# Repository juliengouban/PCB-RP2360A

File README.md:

# PCB-RP2360A
PCB desing file for the new raspberry RP2350A microcontroler

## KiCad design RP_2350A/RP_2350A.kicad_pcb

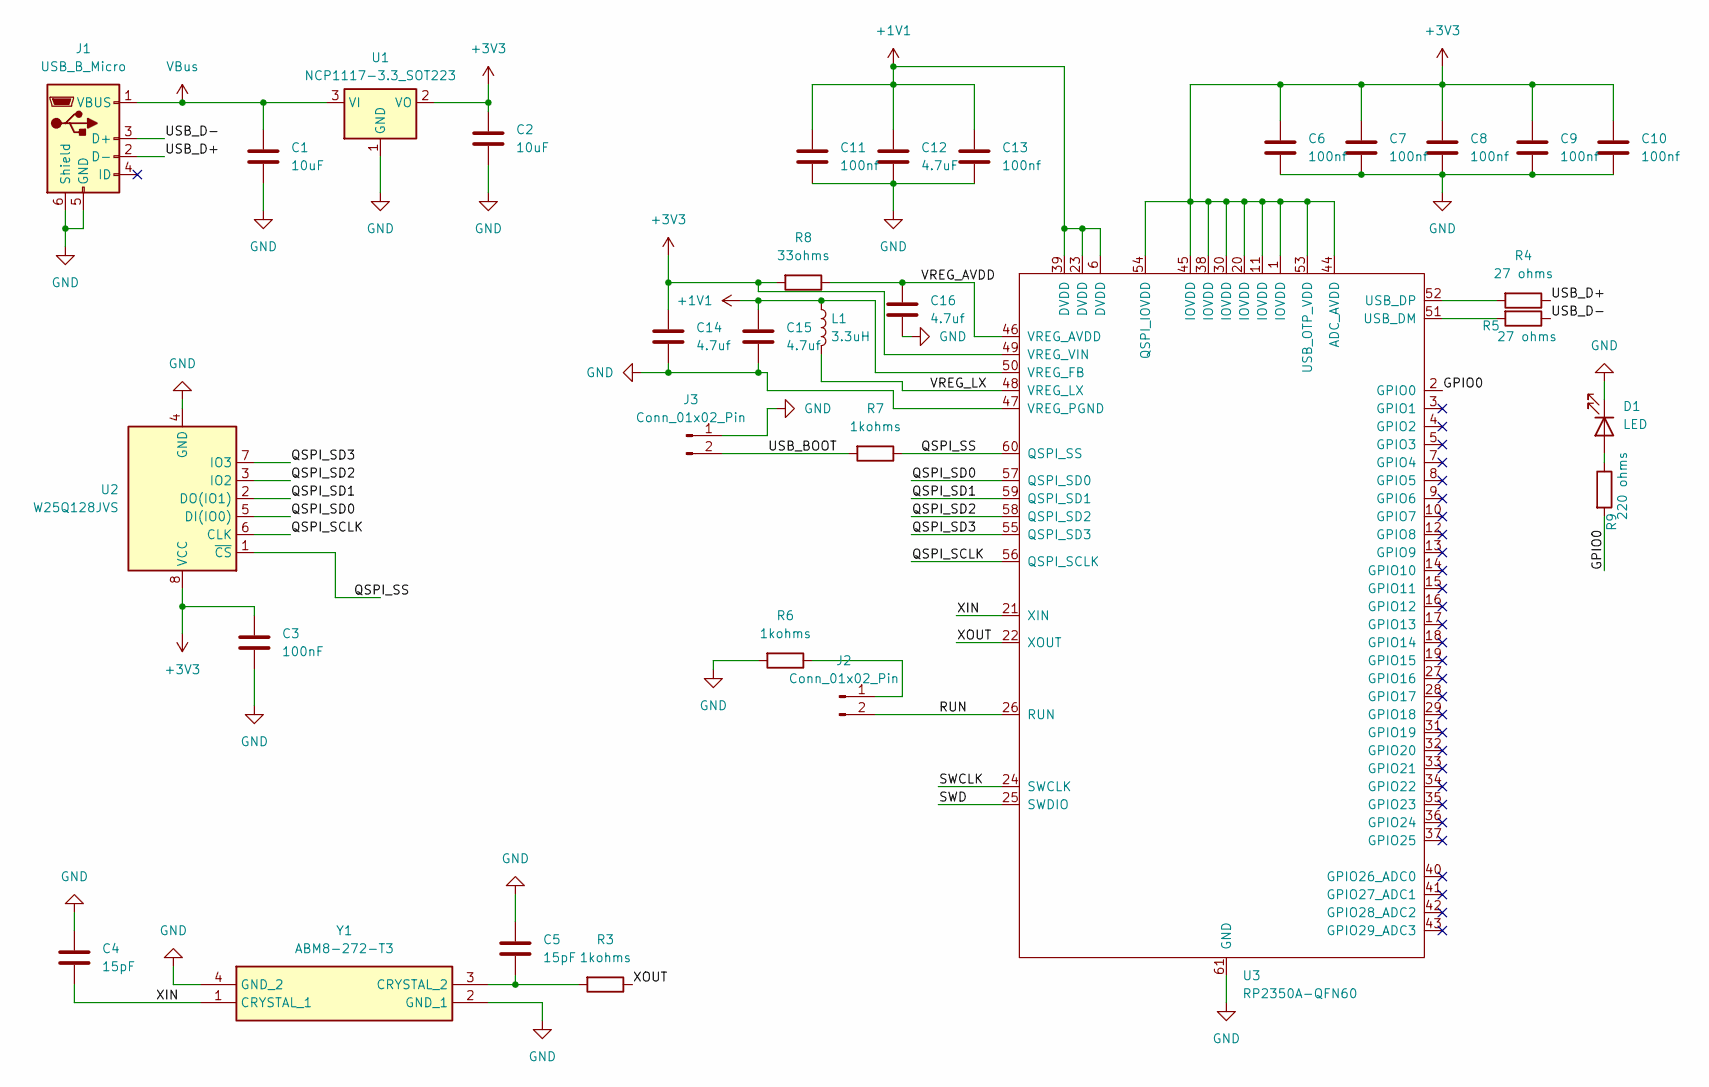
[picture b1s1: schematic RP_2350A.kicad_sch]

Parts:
C1, C2: 10uF; C_0402_1005Metric
C3: 100nF; C_0402_1005Metric
C4, C5: 15pF; C_0402_1005Metric
C6, C7, C8, C9, C10, C11, C13: 100nf; C_0402_1005Metric
C12: 4.7uF; C_0402_1005Metric
C14, C15, C16: 4.7uf; C_0402_1005Metric
D1: LED; LED_0402_1005Metric
J1: USB_B_Micro; USB_Micro-B_Amphenol_10103594-0001LF_Horizontal
J2, J3: Conn_01x02_Pin; PinHeader_1x02_P1.27mm_Vertical
L1: 3.3uH; L_0805_2012Metric
R3, R6, R7: 1kohms; R_0402_1005Metric
R4, R5: 27 ohms; R_0402_1005Metric
R8: 33ohms; R_0402_1005Metric
R9: 220 ohms; R_0402_1005Metric
U1: NCP1117-3.3_SOT223; SOT-223-3_TabPin2
U2: W25Q128JVS; SOIC-8_5.23x5.23mm_P1.27mm
U3: RP2350A-QFN60; RP2350A_QFN-60_EP_7.75x7.75_Pitch0.4mm
Y1: ABM8-272-T3; ABM8272T3; Manufacturer_Part_Number ABM8-272-T3; Mouser Part Number 815-ABM8-272-T3

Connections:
+1V1: C11.1, C12.1, C13.1, C15.1, L1.1, U3.6 (DVDD), U3.23 (DVDD), U3.39 (DVDD), U3.50 (VREG_FB)
+3V3: C2.1, C3.1, C6.1, C7.1, C8.1, C9.1, C10.1, C14.1, R8.2, U1.2 (VO), U2.8 (VCC), U3.1 (IOVDD), U3.11 (IOVDD), U3.20 (IOVDD), U3.30 (IOVDD), U3.38 (IOVDD), U3.44 (ADC_AVDD), U3.45 (IOVDD), U3.49 (VREG_VIN), U3.53 (USB_OTP_VDD), U3.54 (QSPI_IOVDD)
/GPIO0: R9.2, U3.2 (GPIO0)
/QSPI_SCLK: U2.6 (CLK), U3.56 (QSPI_SCLK)
/QSPI_SD0: U2.5 (DI(IO0)), U3.57 (QSPI_SD0)
/QSPI_SD1: U2.2 (DO(IO1)), U3.59 (QSPI_SD1)
/QSPI_SD2: U2.3 (IO2), U3.58 (QSPI_SD2)
/QSPI_SD3: U2.7 (IO3), U3.55 (QSPI_SD3)
/QSPI_SS: R7.1, U2.1 (~CS), U3.60 (QSPI_SS)
/RUN: J2.2, U3.26 (RUN)
/SWCLK: U3.24 (SWCLK)
/SWD: U3.25 (SWDIO)
/USB_BOOT: J3.2, R7.2
/USB_D+: J1.2 (D-), R4.1
/USB_D-: J1.3 (D+), R5.1
/VREG_AVDD: C16.1, R8.1, U3.46 (VREG_AVDD)
/VREG_LX: L1.2, U3.48 (VREG_LX)
/XIN: C4.2, U3.21 (XIN), Y1.1 (CRYSTAL_1)
/XOUT: R3.1, U3.22 (XOUT)
GND: C1.2, C2.2, C3.2, C4.1, C5.2, C6.2, C7.2, C8.2, C9.2, C10.2, C11.2, C12.2, C13.2, C14.2, C15.2, C16.2, D1.1 (K), J1.5 (GND), J1.6 (Shield), J3.1, R6.2, U1.1 (GND), U2.4 (GND), U3.47 (VREG_PGND), U3.61 (GND), Y1.2 (GND_1), Y1.4 (GND_2)
unnamed: D1.2 (A), R9.1
unnamed: J2.1, R6.1
unnamed: R5.2, U3.51 (USB_DM)
unnamed: R4.2, U3.52 (USB_DP)
unnamed: C5.1, R3.2, Y1.3 (CRYSTAL_2)
VBus: C1.1, J1.1 (VBUS), U1.3 (VI)

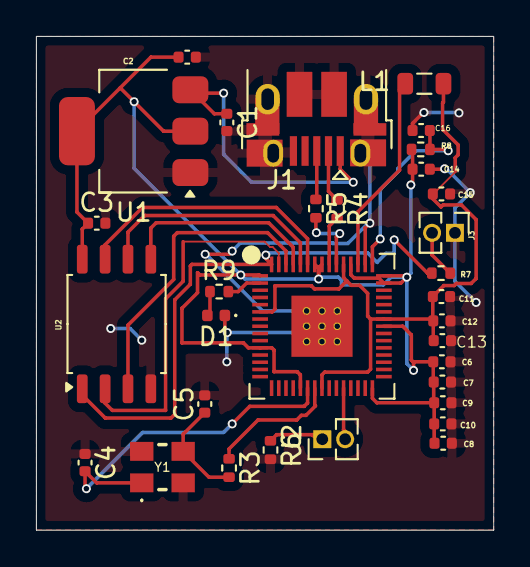
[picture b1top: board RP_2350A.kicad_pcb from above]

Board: 2 copper layers, 25.4 x 27.4 mm, 32 parts (0 on the bottom side), 24 nets.

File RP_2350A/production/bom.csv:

Designator,Footprint,Quantity,Value,LCSC Part #
"C1, C2",0402,2,10uF,
"C10, C11, C13, C3, C6, C7, C8, C9",0402,8,100nf,
"C12, C14, C15, C16",0402,4,4.7uF,
"C4, C5",0402,2,15pF,
D1,0402,1,LED,
J1,USB_Micro-B_Amphenol_10103594-0001LF_Horizontal,1,USB_B_Micro,
"J2, J3",PinHeader_1x02_P1.27mm_Vertical,2,Conn_01x02_Pin,
L1,0805,1,3.3uH,
"R3, R6, R7",0402,3,1kohms,
"R4, R5",0402,2,27 ohms,
R8,0402,1,33ohms,
R9,0402,1,220 ohms,
U1,SOT-223-3_TabPin2,1,NCP1117-3.3_SOT223,
U2,SOIC-8_5.23x5.23mm_P1.27mm,1,W25Q128JVS,
U3,RP2350A_QFN-60_EP_7.75x7.75_Pitch0.4mm,1,RP2350A-QFN60,
Y1,ABM8272T3,1,ABM8-272-T3,
